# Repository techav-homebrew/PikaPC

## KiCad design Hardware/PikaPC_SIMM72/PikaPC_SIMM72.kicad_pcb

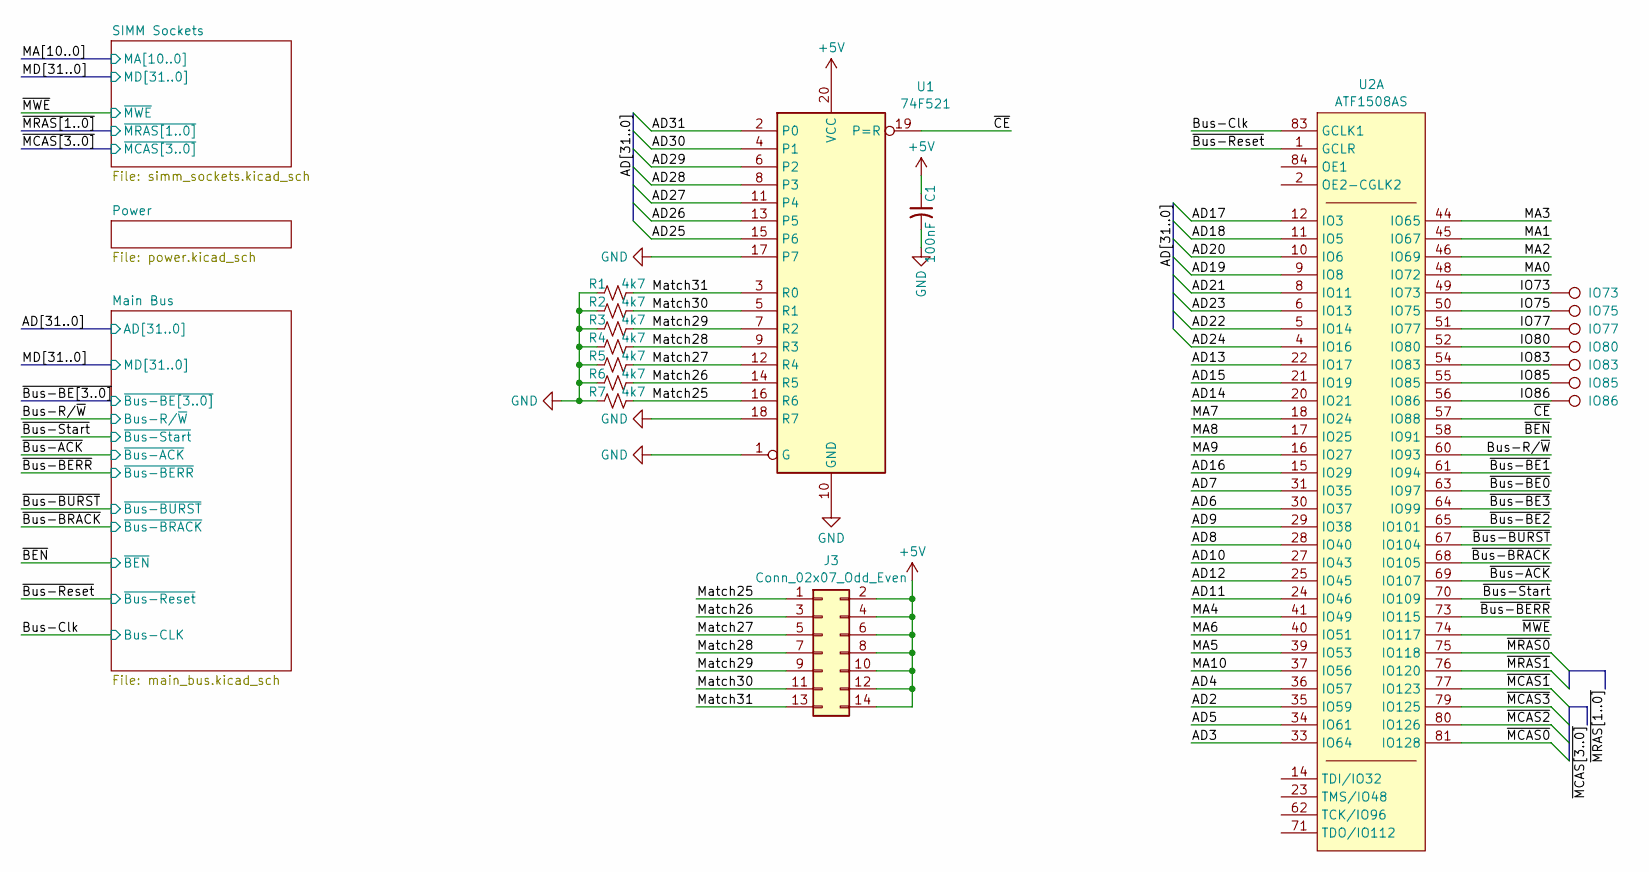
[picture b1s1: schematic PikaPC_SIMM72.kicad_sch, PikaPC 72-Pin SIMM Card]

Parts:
C1: 100nF; C_0805_2012Metric
IO73, IO75, IO77, IO80, IO83, IO85, IO86: TestPoint; PinHeader_1x01_P2.54mm_Vertical
J3: Conn_02x07_Odd_Even; PinHeader_2x07_P2.54mm_Vertical
R1, R2, R3, R4, R5, R6, R7: 4k7; R_0805_2012Metric
U1: 74F521; SOIC-20W_7.5x12.8mm_P1.27mm; Mouser 595-SN74F521DWR
U2: ATF1508AS; PLCC-84_THT-Socket

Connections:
+5V: C1.1, J3.2, J3.4, J3.6, J3.8, J3.10, J3.12, J3.14, U1.20 (VCC); also elsewhere on the board
/AD2: U2.35 (IO59); also elsewhere on the board
/AD3: U2.33 (IO64); also elsewhere on the board
/AD4: U2.36 (IO57); also elsewhere on the board
/AD5: U2.34 (IO61); also elsewhere on the board
/AD6: U2.30 (IO37); also elsewhere on the board
/AD7: U2.31 (IO35); also elsewhere on the board
/AD8: U2.28 (IO40); also elsewhere on the board
/AD9: U2.29 (IO38); also elsewhere on the board
/AD10: U2.27 (IO43); also elsewhere on the board
/AD11: U2.24 (IO46); also elsewhere on the board
/AD12: U2.25 (IO45); also elsewhere on the board
/AD13: U2.22 (IO17); also elsewhere on the board
/AD14: U2.20 (IO21); also elsewhere on the board
/AD15: U2.21 (IO19); also elsewhere on the board
/AD16: U2.15 (IO29); also elsewhere on the board
/AD17: U2.12 (IO3); also elsewhere on the board
/AD18: U2.11 (IO5); also elsewhere on the board
/AD19: U2.9 (IO8); also elsewhere on the board
/AD20: U2.10 (IO6); also elsewhere on the board
/AD21: U2.8 (IO11); also elsewhere on the board
/AD22: U2.5 (IO14); also elsewhere on the board
/AD23: U2.6 (IO13); also elsewhere on the board
/AD24: U2.4 (IO16); also elsewhere on the board
/AD25: U1.15 (P6); also elsewhere on the board
/AD26: U1.13 (P5); also elsewhere on the board
/AD27: U1.11 (P4); also elsewhere on the board
/AD28: U1.8 (P3); also elsewhere on the board
/AD29: U1.6 (P2); also elsewhere on the board
/AD30: U1.4 (P1); also elsewhere on the board
/AD31: U1.2 (P0); also elsewhere on the board
/Bus-Clk: U2.83 (GCLK1); also elsewhere on the board
/Bus-R/~W: U2.60 (IO93); also elsewhere on the board
/IO73: IO73.1, U2.49 (IO73)
/IO75: IO75.1, U2.50 (IO75)
/IO77: IO77.1, U2.51 (IO77)
/IO80: IO80.1, U2.52 (IO80)
/IO83: IO83.1, U2.54 (IO83)
/IO85: IO85.1, U2.55 (IO85)
/IO86: IO86.1, U2.56 (IO86)
/MA0: U2.48 (IO72); also elsewhere on the board
/MA1: U2.45 (IO67); also elsewhere on the board
/MA2: U2.46 (IO69); also elsewhere on the board
/MA3: U2.44 (IO65); also elsewhere on the board
/MA4: U2.41 (IO49); also elsewhere on the board
/MA5: U2.39 (IO53); also elsewhere on the board
/MA6: U2.40 (IO51); also elsewhere on the board
/MA7: U2.18 (IO24); also elsewhere on the board
/MA8: U2.17 (IO25); also elsewhere on the board
/MA9: U2.16 (IO27); also elsewhere on the board
/MA10: U2.37 (IO56); also elsewhere on the board
/Match25: J3.1, R7.2, U1.16 (R6)
/Match26: J3.3, R6.2, U1.14 (R5)
/Match27: J3.5, R5.2, U1.12 (R4)
/Match28: J3.7, R4.2, U1.9 (R3)
/Match29: J3.9, R3.2, U1.7 (R2)
/Match30: J3.11, R2.2, U1.5 (R1)
/Match31: J3.13, R1.2, U1.3 (R0)
/~BEN: U2.58 (IO91); also elsewhere on the board
/~Bus-ACK: U2.69 (IO107); also elsewhere on the board
/~Bus-BE0: U2.63 (IO97); also elsewhere on the board
/~Bus-BE1: U2.61 (IO94); also elsewhere on the board
/~Bus-BE2: U2.65 (IO101); also elsewhere on the board
/~Bus-BE3: U2.64 (IO99); also elsewhere on the board
/~Bus-BERR: U2.73 (IO115); also elsewhere on the board
/~Bus-BRACK: U2.68 (IO105); also elsewhere on the board
/~Bus-BURST: U2.67 (IO104); also elsewhere on the board
/~Bus-Reset: U2.1 (GCLR); also elsewhere on the board
/~Bus-Start: U2.70 (IO109); also elsewhere on the board
/~CE: U1.19 (P=R), U2.57 (IO88)
/~MCAS0: U2.81 (IO128); also elsewhere on the board
/~MCAS1: U2.77 (IO123); also elsewhere on the board
/~MCAS2: U2.80 (IO126); also elsewhere on the board
/~MCAS3: U2.79 (IO125); also elsewhere on the board
/~MRAS0: U2.75 (IO118); also elsewhere on the board
/~MRAS1: U2.76 (IO120); also elsewhere on the board
/~MWE: U2.74 (IO117); also elsewhere on the board
GND: C1.2, R1.1, R2.1, R3.1, R4.1, R5.1, R6.1, R7.1, U1.1 (G), U1.10 (GND), U1.17 (P7), U1.18 (R7); also elsewhere on the board

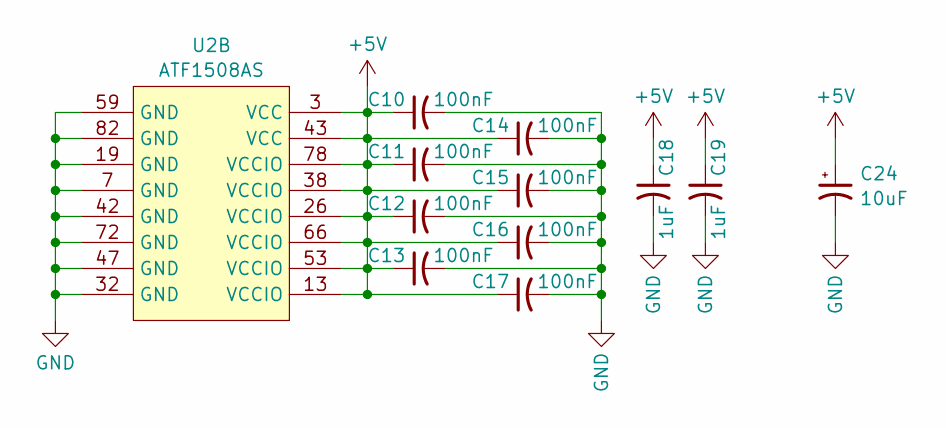
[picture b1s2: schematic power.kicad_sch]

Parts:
C10, C11, C12, C13, C14, C15, C16, C17: 100nF; C_0805_2012Metric; Mouser 187-CL21B104KACNNNC
C18, C19: 1uF; C_0805_2012Metric; Mouser 187-CL21B105KOFNNNG
C24: 10uF; CP_Elec_4x5.7; Mouser 80-EDK106M016A9BAA
U2: ATF1508AS; PLCC-84_THT-Socket

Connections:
+5V: C10.1, C11.1, C12.1, C13.1, C14.1, C15.1, C16.1, C17.1, C18.1, C19.1, C24.1, U2.3 (VCC), U2.13 (VCCIO), U2.26 (VCCIO), U2.38 (VCCIO), U2.43 (VCC), U2.53 (VCCIO), U2.66 (VCCIO), U2.78 (VCCIO); also elsewhere on the board
GND: C10.2, C11.2, C12.2, C13.2, C14.2, C15.2, C16.2, C17.2, C18.2, C19.2, C24.2, U2.7 (GND), U2.19 (GND), U2.32 (GND), U2.42 (GND), U2.47 (GND), U2.59 (GND), U2.72 (GND), U2.82 (GND); also elsewhere on the board

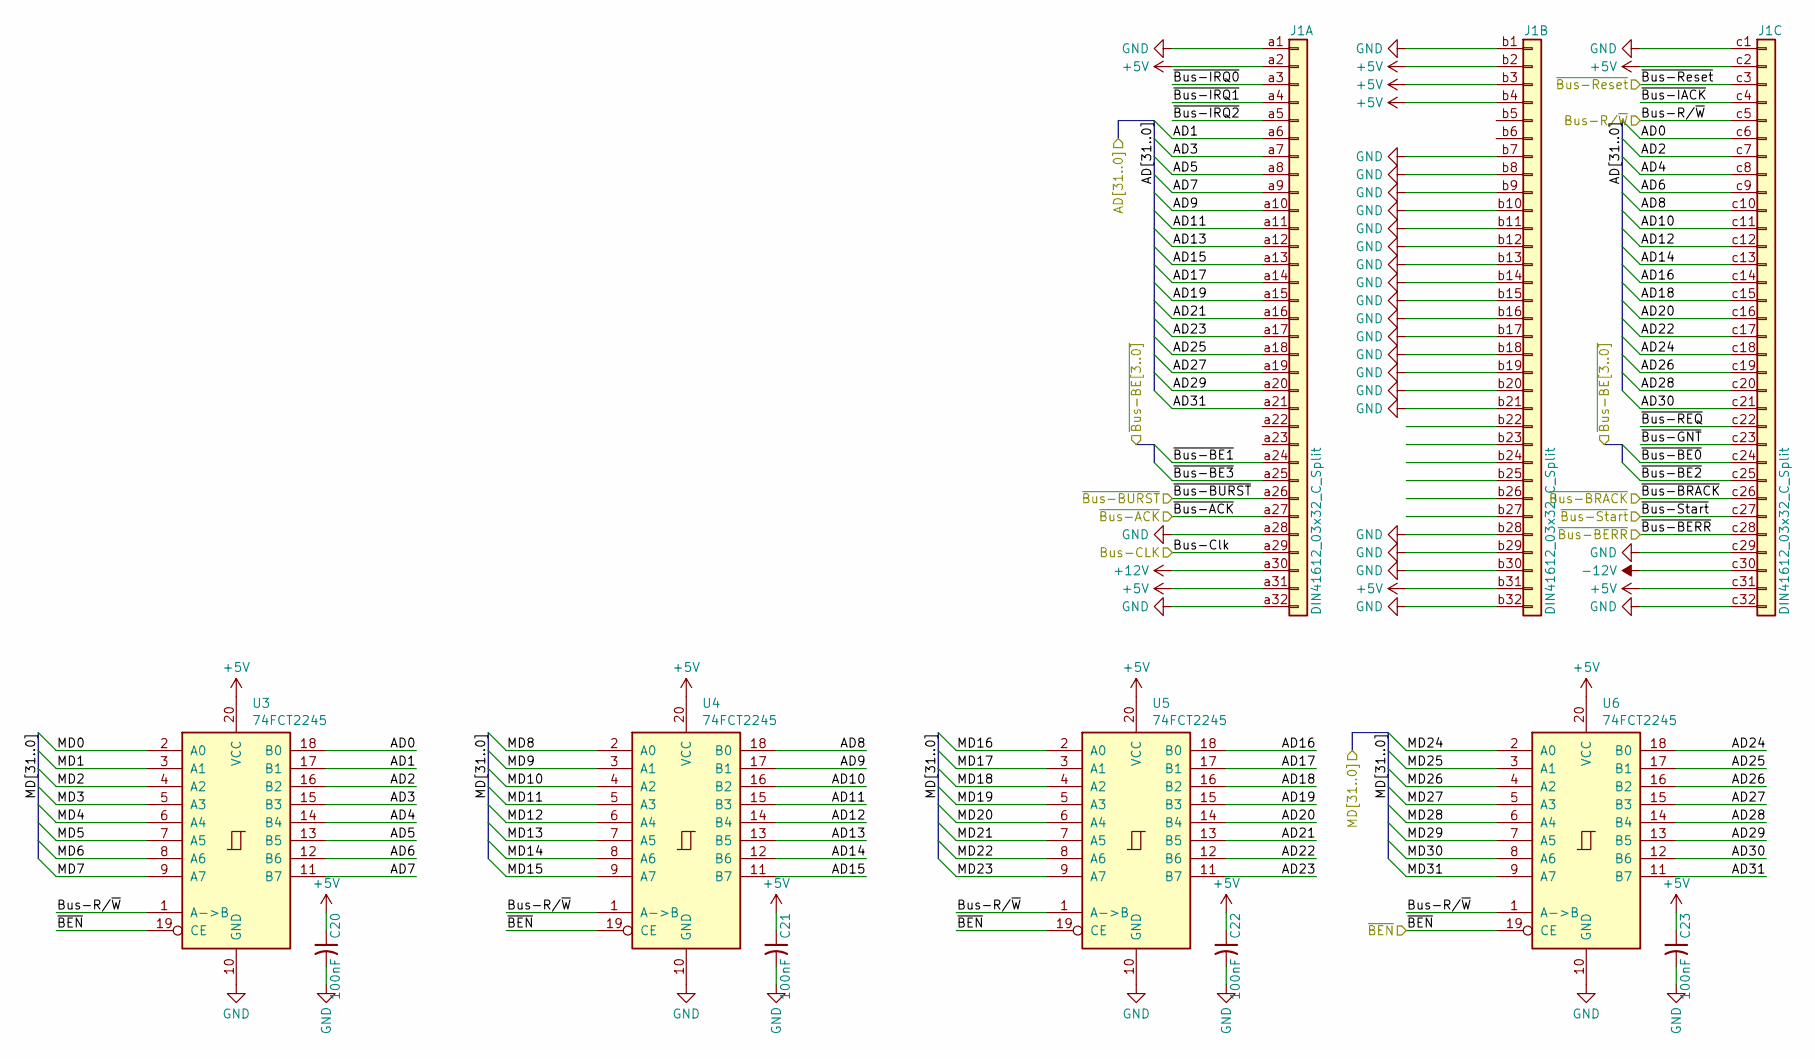
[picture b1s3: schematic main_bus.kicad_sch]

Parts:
C20, C21, C22, C23: 100nF; C_0805_2012Metric
J1: DIN41612_03x32_C_Split; DIN41612_C_3x32_Male_Horizontal_THT
U3, U4, U5, U6: 74FCT2245; SOIC-20W_7.5x12.8mm_P1.27mm

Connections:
+5V: C20.1, C21.1, C22.1, C23.1, J1.a2, J1.a31, J1.b2, J1.b3, J1.b4, J1.b31, J1.c2, J1.c31, U3.20 (VCC), U4.20 (VCC), U5.20 (VCC), U6.20 (VCC); also elsewhere on the board
+12V: J1.a30
-12V: J1.c30
/AD0: J1.c6, U3.18 (B0)
/AD1: J1.a6, U3.17 (B1)
/AD2: J1.c7, U3.16 (B2); also elsewhere on the board
/AD3: J1.a7, U3.15 (B3); also elsewhere on the board
/AD4: J1.c8, U3.14 (B4); also elsewhere on the board
/AD5: J1.a8, U3.13 (B5); also elsewhere on the board
/AD6: J1.c9, U3.12 (B6); also elsewhere on the board
/AD7: J1.a9, U3.11 (B7); also elsewhere on the board
/AD8: J1.c10, U4.18 (B0); also elsewhere on the board
/AD9: J1.a10, U4.17 (B1); also elsewhere on the board
/AD10: J1.c11, U4.16 (B2); also elsewhere on the board
/AD11: J1.a11, U4.15 (B3); also elsewhere on the board
/AD12: J1.c12, U4.14 (B4); also elsewhere on the board
/AD13: J1.a12, U4.13 (B5); also elsewhere on the board
/AD14: J1.c13, U4.12 (B6); also elsewhere on the board
/AD15: J1.a13, U4.11 (B7); also elsewhere on the board
/AD16: J1.c14, U5.18 (B0); also elsewhere on the board
/AD17: J1.a14, U5.17 (B1); also elsewhere on the board
/AD18: J1.c15, U5.16 (B2); also elsewhere on the board
/AD19: J1.a15, U5.15 (B3); also elsewhere on the board
/AD20: J1.c16, U5.14 (B4); also elsewhere on the board
/AD21: J1.a16, U5.13 (B5); also elsewhere on the board
/AD22: J1.c17, U5.12 (B6); also elsewhere on the board
/AD23: J1.a17, U5.11 (B7); also elsewhere on the board
/AD24: J1.c18, U6.18 (B0); also elsewhere on the board
/AD25: J1.a18, U6.17 (B1); also elsewhere on the board
/AD26: J1.c19, U6.16 (B2); also elsewhere on the board
/AD27: J1.a19, U6.15 (B3); also elsewhere on the board
/AD28: J1.c20, U6.14 (B4); also elsewhere on the board
/AD29: J1.a20, U6.13 (B5); also elsewhere on the board
/AD30: J1.c21, U6.12 (B6); also elsewhere on the board
/AD31: J1.a21, U6.11 (B7); also elsewhere on the board
/Bus-Clk: J1.a29; also elsewhere on the board
/Bus-R/~W: J1.c5, U3.1 (A->B), U4.1 (A->B), U5.1 (A->B), U6.1 (A->B); also elsewhere on the board
/MD0: U3.2 (A0); also elsewhere on the board
/MD1: U3.3 (A1); also elsewhere on the board
/MD2: U3.4 (A2); also elsewhere on the board
/MD3: U3.5 (A3); also elsewhere on the board
/MD4: U3.6 (A4); also elsewhere on the board
/MD5: U3.7 (A5); also elsewhere on the board
/MD6: U3.8 (A6); also elsewhere on the board
/MD7: U3.9 (A7); also elsewhere on the board
/MD8: U4.2 (A0); also elsewhere on the board
/MD9: U4.3 (A1); also elsewhere on the board
/MD10: U4.4 (A2); also elsewhere on the board
/MD11: U4.5 (A3); also elsewhere on the board
/MD12: U4.6 (A4); also elsewhere on the board
/MD13: U4.7 (A5); also elsewhere on the board
/MD14: U4.8 (A6); also elsewhere on the board
/MD15: U4.9 (A7); also elsewhere on the board
/MD16: U5.2 (A0); also elsewhere on the board
/MD17: U5.3 (A1); also elsewhere on the board
/MD18: U5.4 (A2); also elsewhere on the board
/MD19: U5.5 (A3); also elsewhere on the board
/MD20: U5.6 (A4); also elsewhere on the board
/MD21: U5.7 (A5); also elsewhere on the board
/MD22: U5.8 (A6); also elsewhere on the board
/MD23: U5.9 (A7); also elsewhere on the board
/MD24: U6.2 (A0); also elsewhere on the board
/MD25: U6.3 (A1); also elsewhere on the board
/MD26: U6.4 (A2); also elsewhere on the board
/MD27: U6.5 (A3); also elsewhere on the board
/MD28: U6.6 (A4); also elsewhere on the board
/MD29: U6.7 (A5); also elsewhere on the board
/MD30: U6.8 (A6); also elsewhere on the board
/MD31: U6.9 (A7); also elsewhere on the board
/Main Bus/~Bus-GNT: J1.c23
/Main Bus/~Bus-IACK: J1.c4
/Main Bus/~Bus-IRQ0: J1.a3
/Main Bus/~Bus-IRQ1: J1.a4
/Main Bus/~Bus-IRQ2: J1.a5
/Main Bus/~Bus-REQ: J1.c22
/~BEN: U3.19 (CE), U4.19 (CE), U5.19 (CE), U6.19 (CE); also elsewhere on the board
/~Bus-ACK: J1.a27; also elsewhere on the board
/~Bus-BE0: J1.c24; also elsewhere on the board
/~Bus-BE1: J1.a24; also elsewhere on the board
/~Bus-BE2: J1.c25; also elsewhere on the board
/~Bus-BE3: J1.a25; also elsewhere on the board
/~Bus-BERR: J1.c28; also elsewhere on the board
/~Bus-BRACK: J1.c26; also elsewhere on the board
/~Bus-BURST: J1.a26; also elsewhere on the board
/~Bus-Reset: J1.c3; also elsewhere on the board
/~Bus-Start: J1.c27; also elsewhere on the board
GND: C20.2, C21.2, C22.2, C23.2, J1.a1, J1.a28, J1.a32, J1.b1, J1.b7, J1.b8, J1.b9, J1.b10, J1.b11, J1.b12, J1.b13, J1.b14, J1.b15, J1.b16, J1.b17, J1.b18, J1.b19, J1.b20, J1.b21, J1.b28, J1.b29, J1.b30, J1.b32, J1.c1, J1.c29, J1.c32, U3.10 (GND), U4.10 (GND), U5.10 (GND), U6.10 (GND); also elsewhere on the board

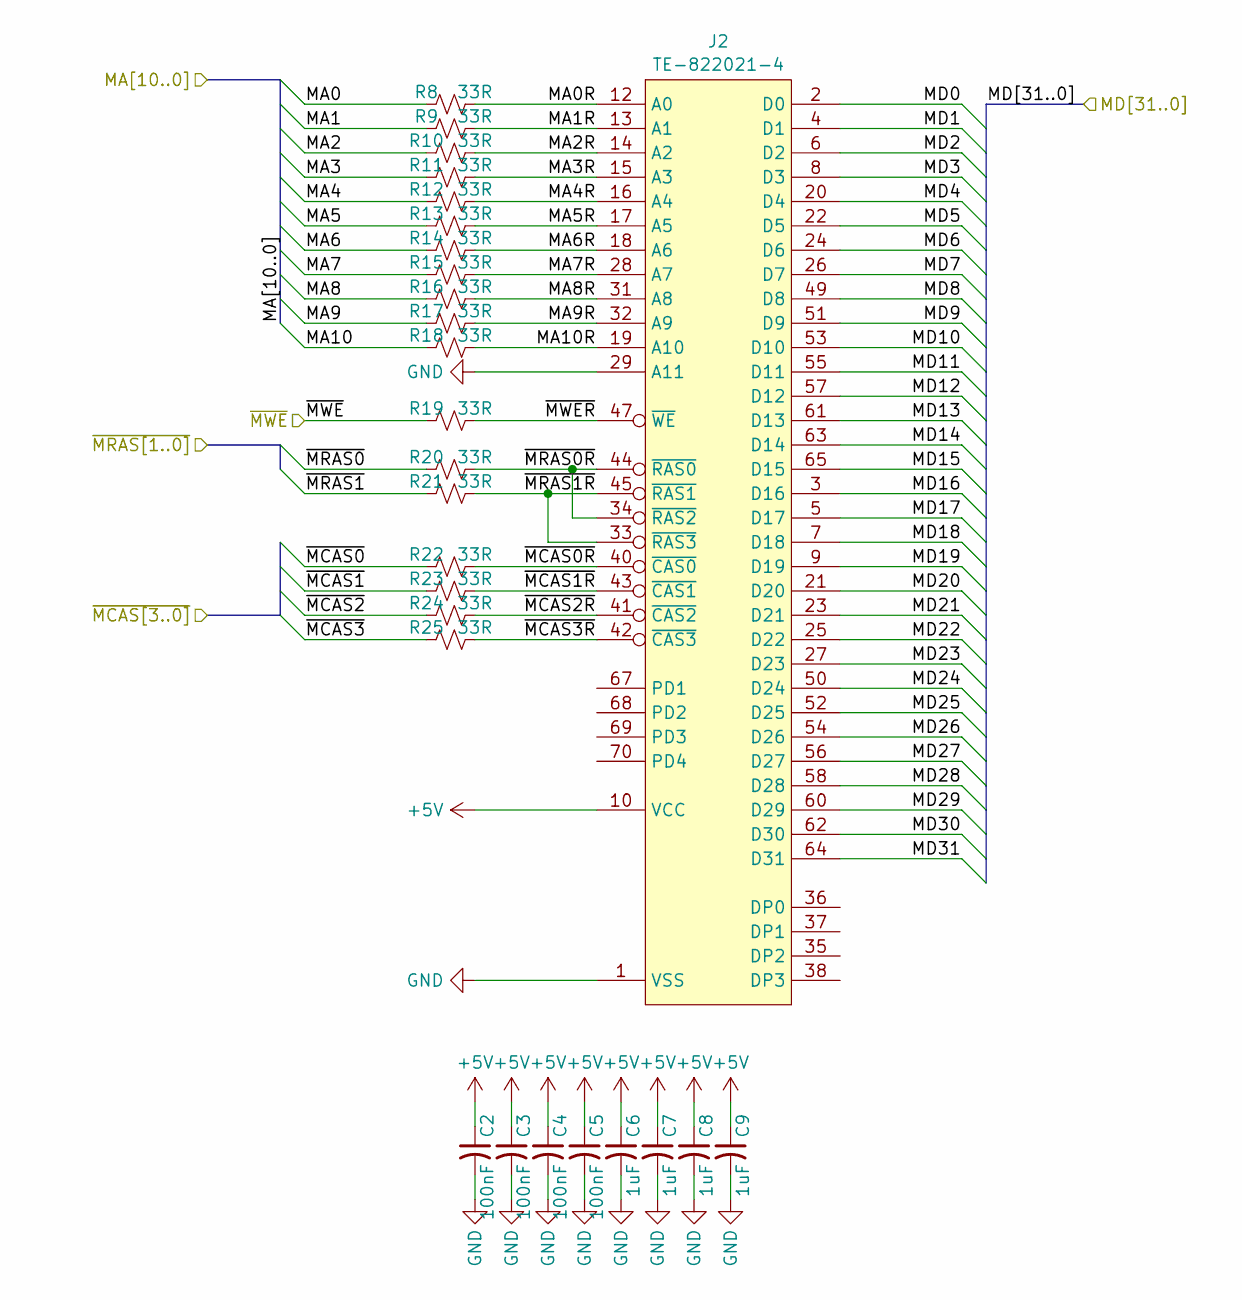
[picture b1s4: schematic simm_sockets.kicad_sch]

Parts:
C2, C3, C4, C5: 100nF; C_0805_2012Metric
C6, C7, C8, C9: 1uF; C_0805_2012Metric
J2: TE-822021-4; SIMM72
R8, R9, R10, R11, R12, R13, R14, R15, R16, R17, R18, R19, R20, R21, R22, R23, R24, R25: 33R; R_0805_2012Metric

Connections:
+5V: C2.1, C3.1, C4.1, C5.1, C6.1, C7.1, C8.1, C9.1, J2.10 (VCC), J2.30 (VCC), J2.59 (VCC); also elsewhere on the board
/MA0: R8.1; also elsewhere on the board
/MA1: R9.1; also elsewhere on the board
/MA2: R10.1; also elsewhere on the board
/MA3: R11.1; also elsewhere on the board
/MA4: R12.1; also elsewhere on the board
/MA5: R13.1; also elsewhere on the board
/MA6: R14.1; also elsewhere on the board
/MA7: R15.1; also elsewhere on the board
/MA8: R16.1; also elsewhere on the board
/MA9: R17.1; also elsewhere on the board
/MA10: R18.1; also elsewhere on the board
/MD0: J2.2 (D0); also elsewhere on the board
/MD1: J2.4 (D1); also elsewhere on the board
/MD2: J2.6 (D2); also elsewhere on the board
/MD3: J2.8 (D3); also elsewhere on the board
/MD4: J2.20 (D4); also elsewhere on the board
/MD5: J2.22 (D5); also elsewhere on the board
/MD6: J2.24 (D6); also elsewhere on the board
/MD7: J2.26 (D7); also elsewhere on the board
/MD8: J2.49 (D8); also elsewhere on the board
/MD9: J2.51 (D9); also elsewhere on the board
/MD10: J2.53 (D10); also elsewhere on the board
/MD11: J2.55 (D11); also elsewhere on the board
/MD12: J2.57 (D12); also elsewhere on the board
/MD13: J2.61 (D13); also elsewhere on the board
/MD14: J2.63 (D14); also elsewhere on the board
/MD15: J2.65 (D15); also elsewhere on the board
/MD16: J2.3 (D16); also elsewhere on the board
/MD17: J2.5 (D17); also elsewhere on the board
/MD18: J2.7 (D18); also elsewhere on the board
/MD19: J2.9 (D19); also elsewhere on the board
/MD20: J2.21 (D20); also elsewhere on the board
/MD21: J2.23 (D21); also elsewhere on the board
/MD22: J2.25 (D22); also elsewhere on the board
/MD23: J2.27 (D23); also elsewhere on the board
/MD24: J2.50 (D24); also elsewhere on the board
/MD25: J2.52 (D25); also elsewhere on the board
/MD26: J2.54 (D26); also elsewhere on the board
/MD27: J2.56 (D27); also elsewhere on the board
/MD28: J2.58 (D28); also elsewhere on the board
/MD29: J2.60 (D29); also elsewhere on the board
/MD30: J2.62 (D30); also elsewhere on the board
/MD31: J2.64 (D31); also elsewhere on the board
/SIMM Sockets/MA0R: J2.12 (A0), R8.2
/SIMM Sockets/MA1R: J2.13 (A1), R9.2
/SIMM Sockets/MA2R: J2.14 (A2), R10.2
/SIMM Sockets/MA3R: J2.15 (A3), R11.2
/SIMM Sockets/MA4R: J2.16 (A4), R12.2
/SIMM Sockets/MA5R: J2.17 (A5), R13.2
/SIMM Sockets/MA6R: J2.18 (A6), R14.2
/SIMM Sockets/MA7R: J2.28 (A7), R15.2
/SIMM Sockets/MA8R: J2.31 (A8), R16.2
/SIMM Sockets/MA9R: J2.32 (A9), R17.2
/SIMM Sockets/MA10R: J2.19 (A10), R18.2
/SIMM Sockets/~MCAS0R: J2.40 (~CAS0), R22.2
/SIMM Sockets/~MCAS1R: J2.43 (~CAS1), R23.2
/SIMM Sockets/~MCAS2R: J2.41 (~CAS2), R24.2
/SIMM Sockets/~MCAS3R: J2.42 (~CAS3), R25.2
/SIMM Sockets/~MRAS0R: J2.34 (~RAS2), J2.44 (~RAS0), R20.2
/SIMM Sockets/~MRAS1R: J2.33 (~RAS3), J2.45 (~RAS1), R21.2
/SIMM Sockets/~MWER: J2.47 (~WE), R19.2
/~MCAS0: R22.1; also elsewhere on the board
/~MCAS1: R23.1; also elsewhere on the board
/~MCAS2: R24.1; also elsewhere on the board
/~MCAS3: R25.1; also elsewhere on the board
/~MRAS0: R20.1; also elsewhere on the board
/~MRAS1: R21.1; also elsewhere on the board
/~MWE: R19.1; also elsewhere on the board
GND: C2.2, C3.2, C4.2, C5.2, C6.2, C7.2, C8.2, C9.2, J2.1 (VSS), J2.29 (A11), J2.39 (VSS), J2.72 (VSS); also elsewhere on the board

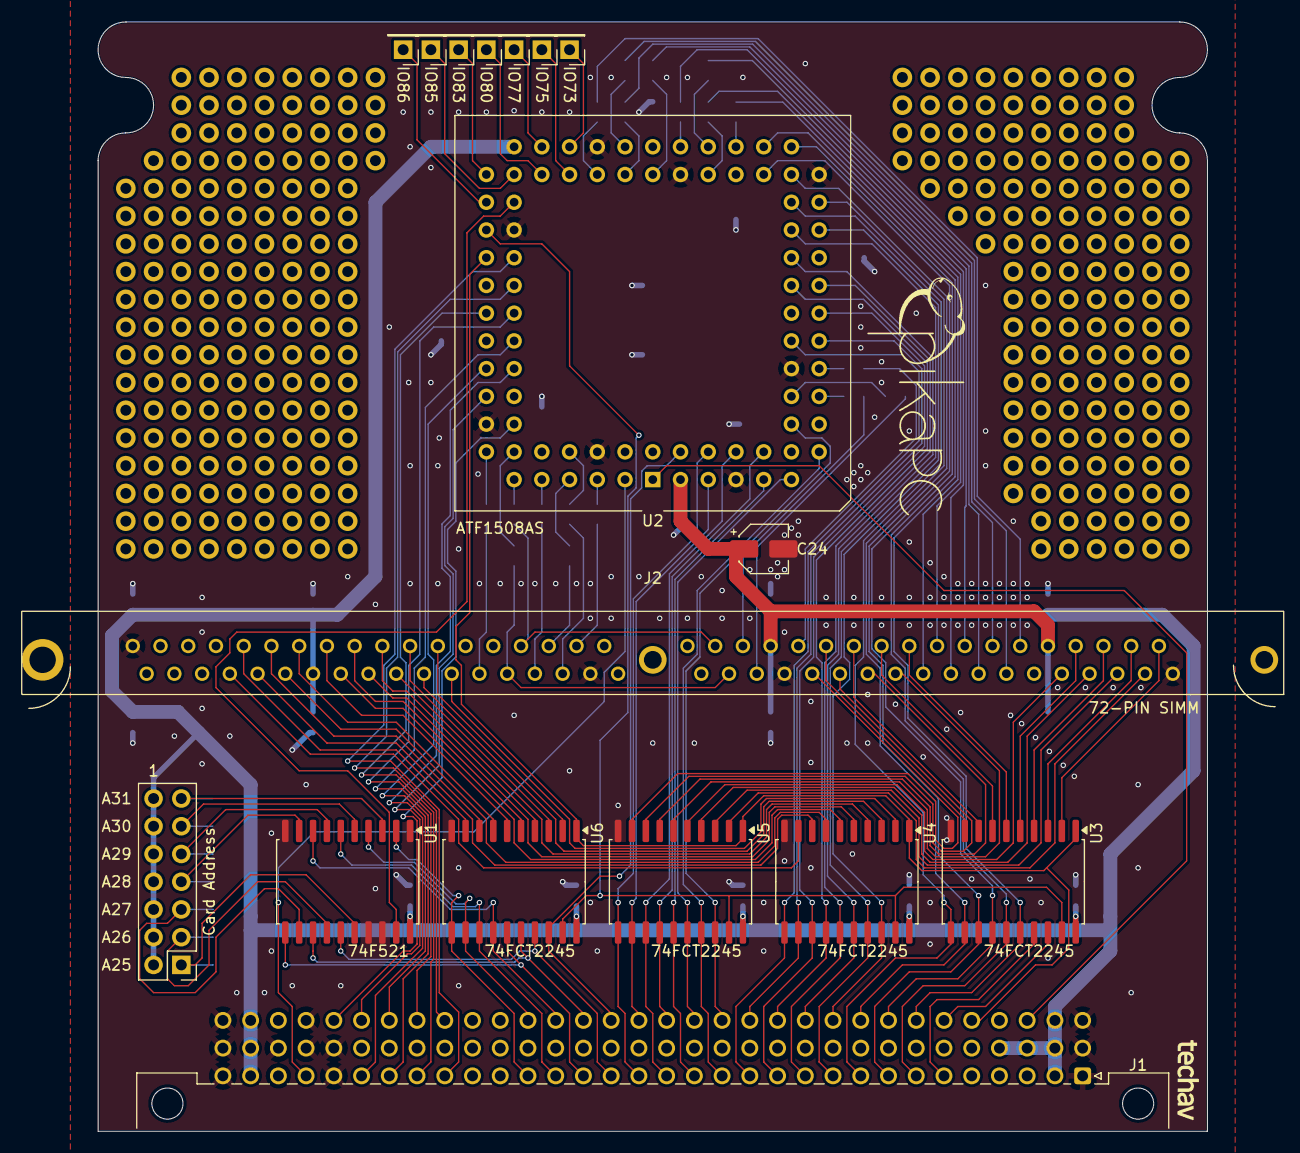
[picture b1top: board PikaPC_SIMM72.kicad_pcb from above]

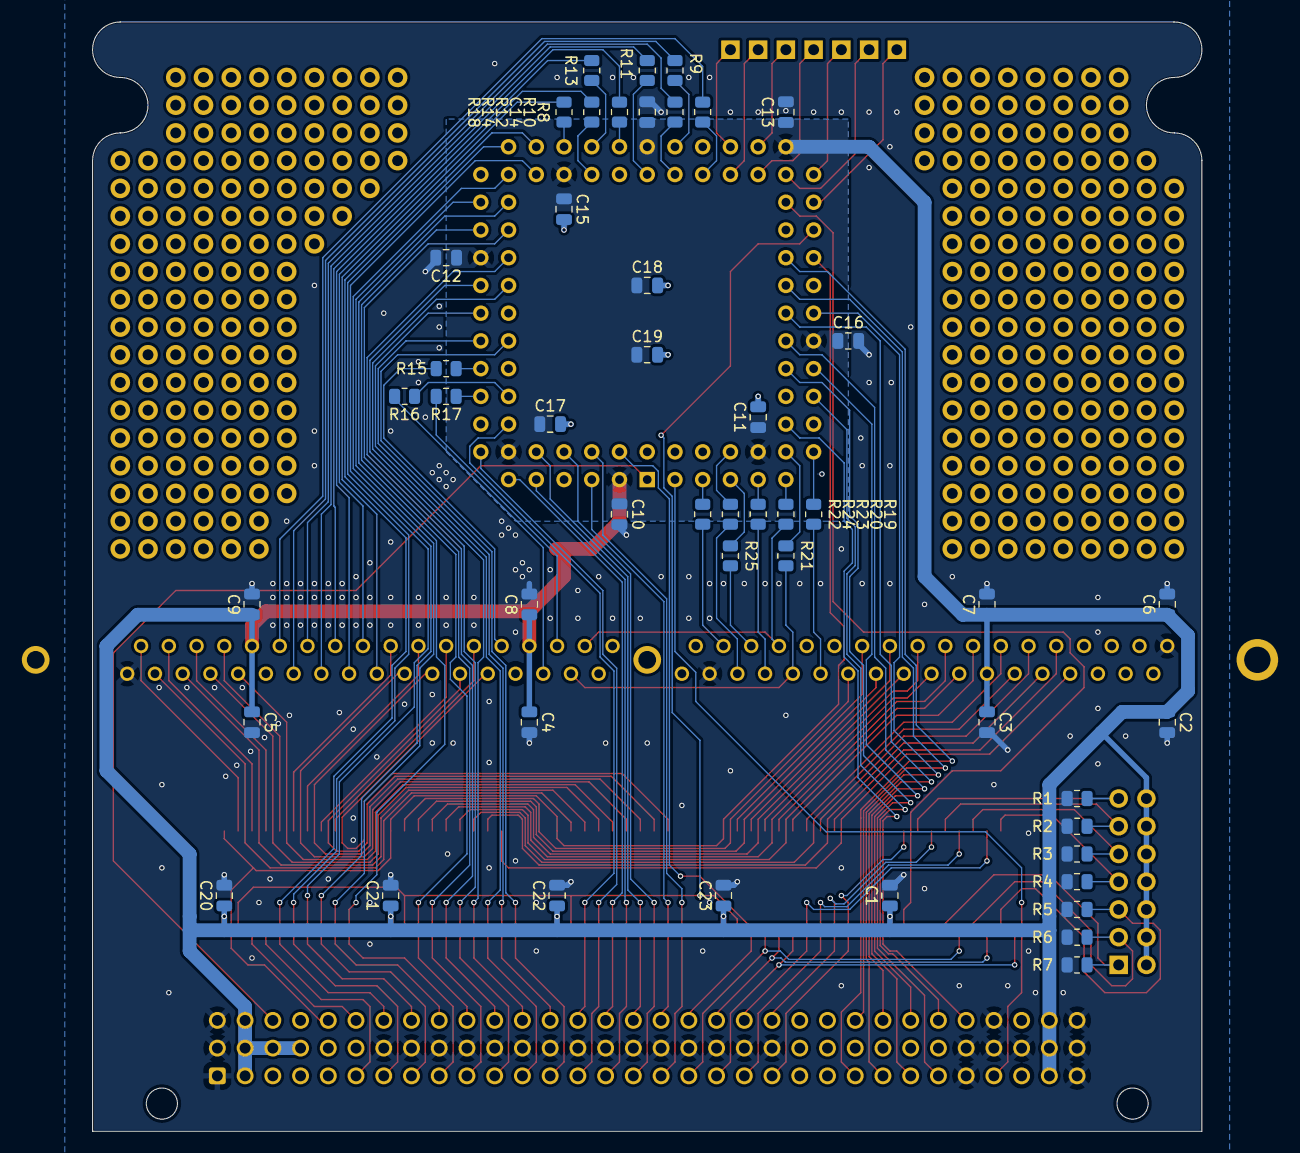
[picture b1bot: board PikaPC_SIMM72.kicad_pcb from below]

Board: 2 copper layers, 101.6 x 101.6 mm, 65 parts (48 on the bottom side), 130 nets.
